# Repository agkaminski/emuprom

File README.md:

# emuprom
DIY ATmega8 based 27C256 EPROM emulator. Human accessible UART interface
(19200N1, CH340 on USB C).

Revision D has been verified and it is working as intended (working both with
TL866 EPROM programer and FellaPC computer).

# Target connection
Via ribbon cable with DIP-28 adapter. Uses 40 pin IDC connector, but only 28
pins are used. Target power state detection is supported (external bus is
resistant to the target high-z bus state).

Crude cable schematic, top view (should be enough to be able to make this cable):

Sanity check - EPROM GND (pin \#14) should be on the one before last wire (bottom of the picture).

# UART interface
Available via USB C UART port, 19200 baud, no parity, 1 stop bit. Interface is
human friendly, but also easy to script. Available commands:

- ? - help
- ! - claim bus, memory edit, assert /RST
- . - release bus, deassert /RST
- @ - set address mode
- \# - set data mode
- = - dump 256 bytes @addres
- t - memory test
- \+ - echo on
- \- echo off
- m - calculate md5 sum
- s - clear memory (all 0xff)
- r - reset target (pulse /RST)

Example sequence with comments:
- \- echo disable,
- ! - claims the bus,
- @0000 - sets address to zero,
- \# - selects data mode,
- 0102030405060708 - 8 bytes are written at address 0,
- . - release the bus and start the target,
- \+ - enable echo.

Or all at once: -!@0000#0102030405060708.+

# Uploading FW
avr-gcc, avr-libc and avrdude are needed.

- make (build FW),
- make fuse (set fuses to set internal RC @8MHz),
- make install (upload FW).

# Pictures
This is a picture of revision D. Note the recommended heat shrink sleeve, to
prevent accidental short circuits.

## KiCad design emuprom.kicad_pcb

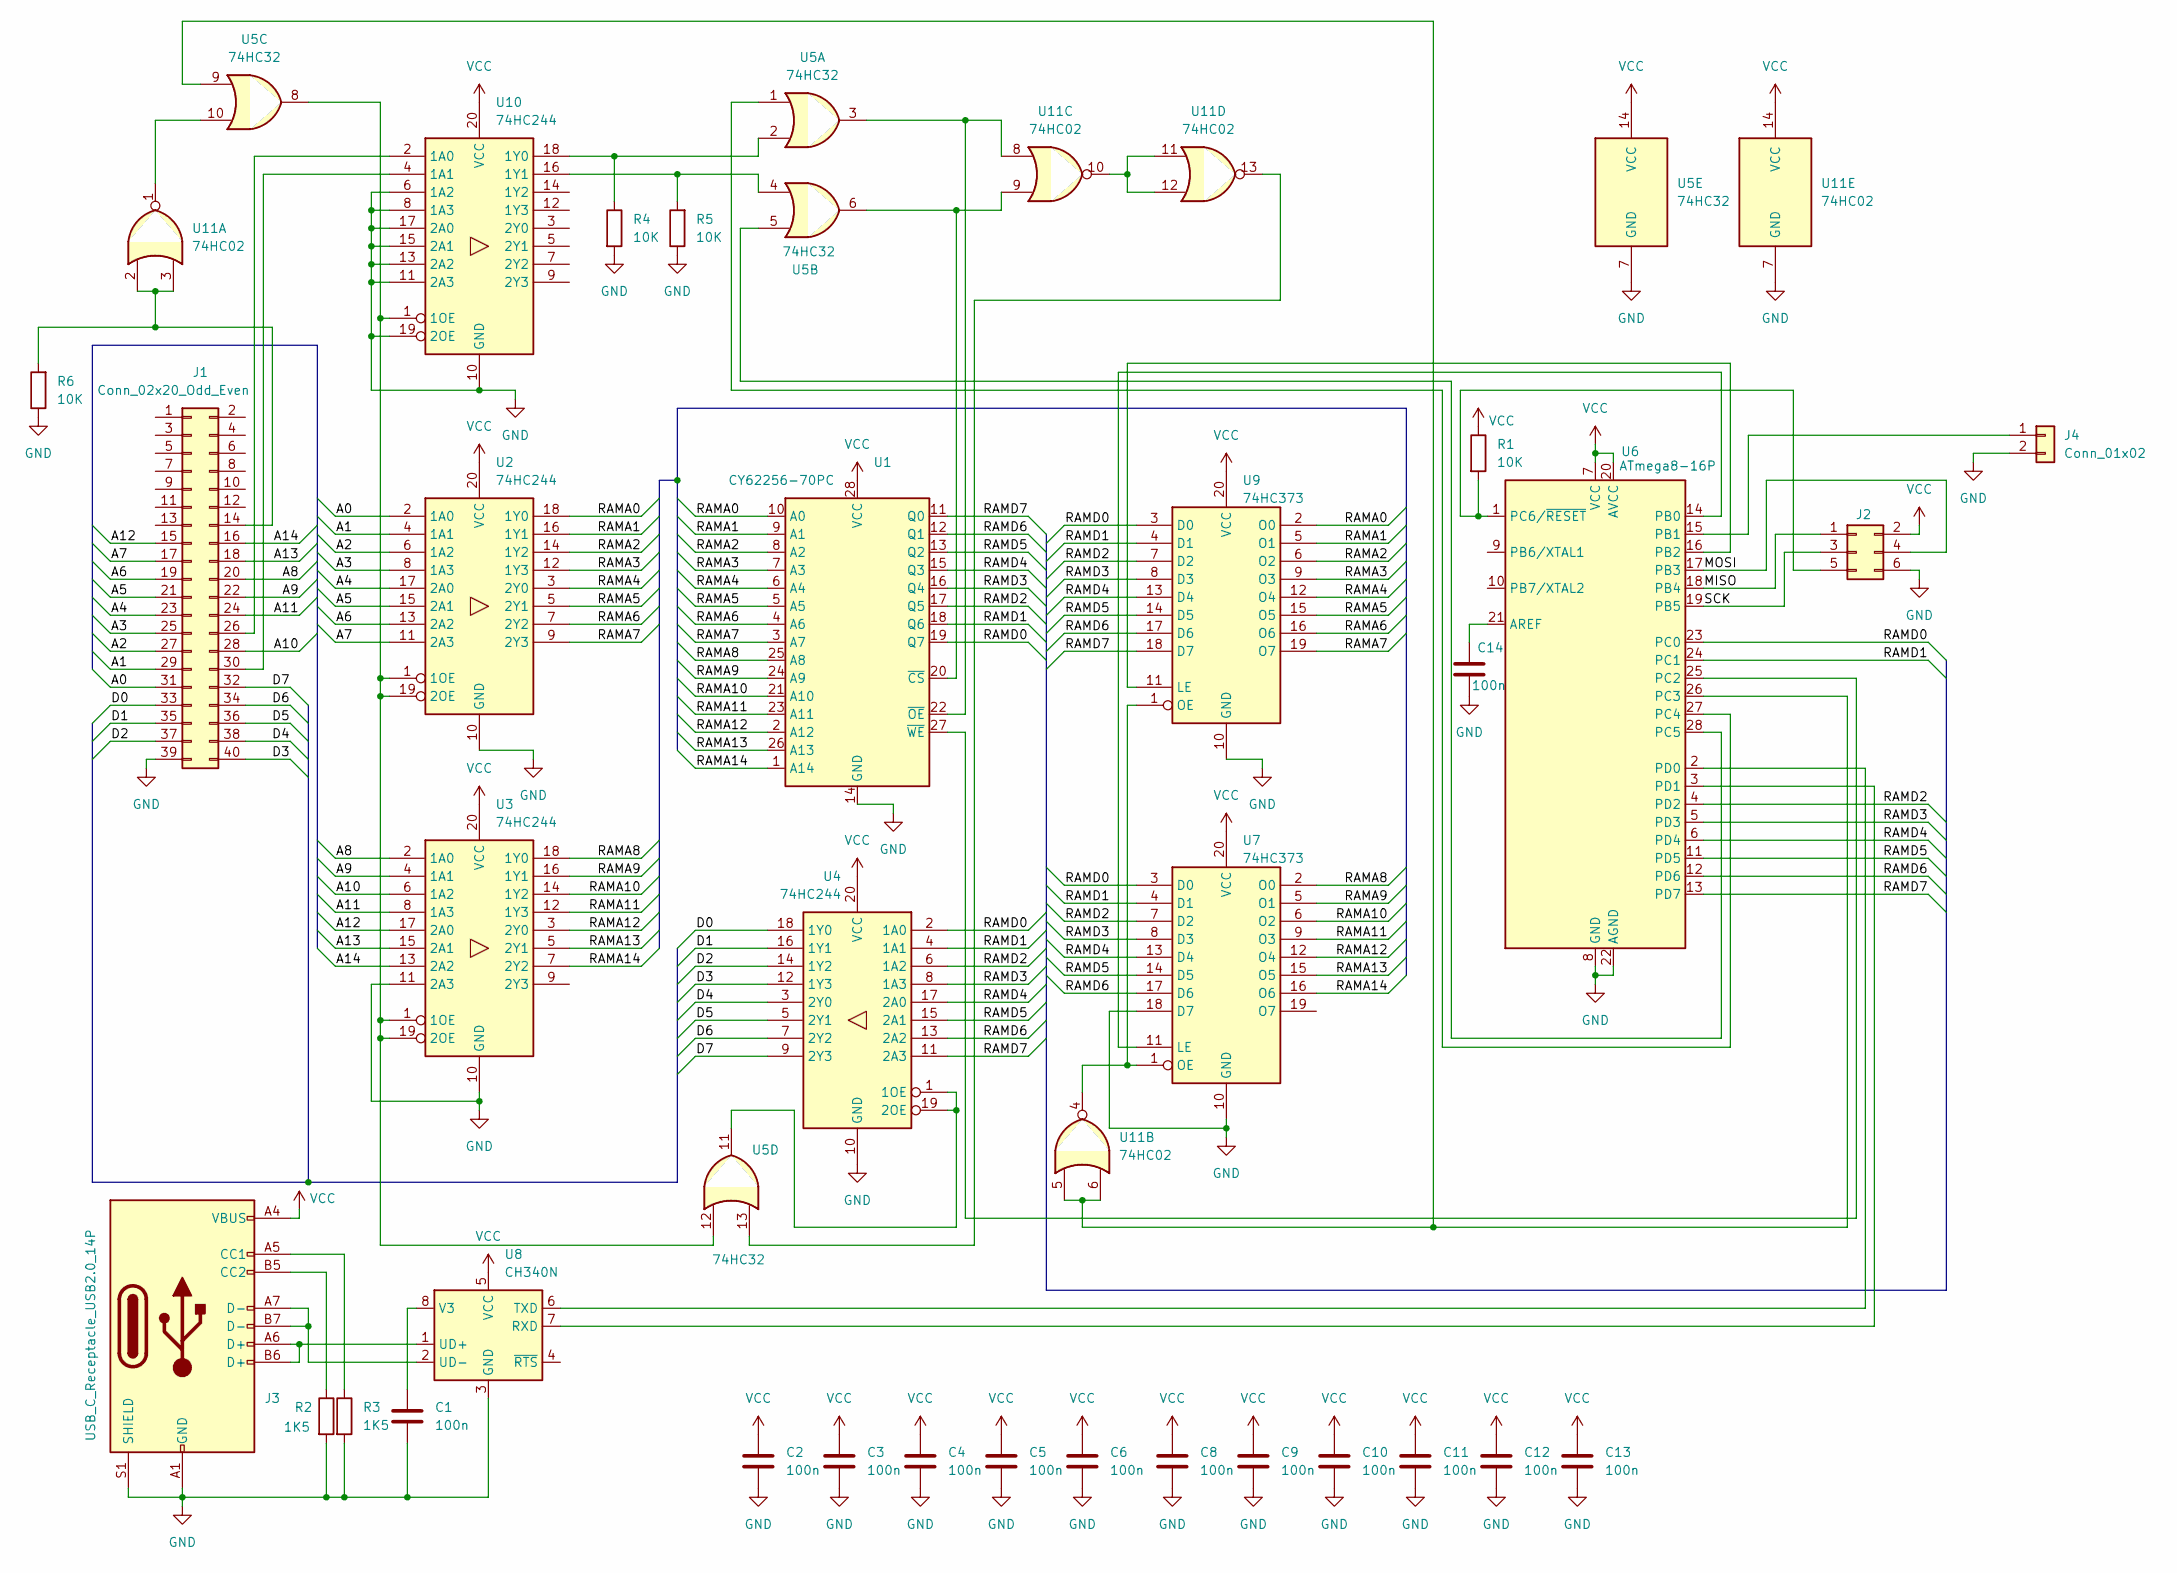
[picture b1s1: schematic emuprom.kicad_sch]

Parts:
C1, C2, C3, C4, C5, C6, C8, C9, C10, C11, C12, C13, C14: 100n; C_Disc_D3.0mm_W1.6mm_P2.50mm
J1: Conn_02x20_Odd_Even; IDC-Header_2x20_P2.54mm_Horizontal
J2: Conn_02x03_Odd_Even; IDC-Header_2x03_P2.54mm_Vertical
J3: USB_C_Receptacle_USB2.0_14P; USB_C_Receptacle_GCT_USB4105-xx-A_16P_TopMnt_Horizontal
J4: Conn_01x02; PinHeader_1x02_P2.54mm_Horizontal
R1, R4, R5, R6: 10K; R_Axial_DIN0207_L6.3mm_D2.5mm_P7.62mm_Horizontal
R2, R3: 1K5; R_Axial_DIN0207_L6.3mm_D2.5mm_P7.62mm_Horizontal
U1: CY62256-70PC; DIP-28_W15.24mm
U2, U3, U4, U10: 74HC244; DIP-20_W7.62mm
U5: 74HC32; DIP-14_W7.62mm
U6: ATmega8-16P; DIP-28_W7.62mm
U7, U9: 74HC373; DIP-20_W7.62mm
U8: CH340N; SOP-8_3.9x4.9mm_P1.27mm
U11: 74HC02; DIP-14_W7.62mm

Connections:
/A0: J1.31, U2.2 (1A0)
/A1: J1.29, U2.4 (1A1)
/A2: J1.27, U2.6 (1A2)
/A3: J1.25, U2.8 (1A3)
/A4: J1.23, U2.17 (2A0)
/A5: J1.21, U2.15 (2A1)
/A6: J1.19, U2.13 (2A2)
/A7: J1.17, U2.11 (2A3)
/A8: J1.20, U3.2 (1A0)
/A9: J1.22, U3.4 (1A1)
/A10: J1.28, U3.6 (1A2)
/A11: J1.24, U3.8 (1A3)
/A12: J1.15, U3.17 (2A0)
/A13: J1.18, U3.15 (2A1)
/A14: J1.16, U3.13 (2A2)
/D0: J1.33, U4.18 (1Y0)
/D1: J1.35, U4.16 (1Y1)
/D2: J1.37, U4.14 (1Y2)
/D3: J1.40, U4.12 (1Y3)
/D4: J1.38, U4.3 (2Y0)
/D5: J1.36, U4.5 (2Y1)
/D6: J1.34, U4.7 (2Y2)
/D7: J1.32, U4.9 (2Y3)
/MISO: J2.1, U6.18 (PB4)
/MOSI: J2.4, U6.17 (PB3)
/RAMA0: U1.10 (A0), U2.18 (1Y0), U9.2 (O0)
/RAMA1: U1.9 (A1), U2.16 (1Y1), U9.5 (O1)
/RAMA2: U1.8 (A2), U2.14 (1Y2), U9.6 (O2)
/RAMA3: U1.7 (A3), U2.12 (1Y3), U9.9 (O3)
/RAMA4: U1.6 (A4), U2.3 (2Y0), U9.12 (O4)
/RAMA5: U1.5 (A5), U2.5 (2Y1), U9.15 (O5)
/RAMA6: U1.4 (A6), U2.7 (2Y2), U9.16 (O6)
/RAMA7: U1.3 (A7), U2.9 (2Y3), U9.19 (O7)
/RAMA8: U1.25 (A8), U3.18 (1Y0), U7.2 (O0)
/RAMA9: U1.24 (A9), U3.16 (1Y1), U7.5 (O1)
/RAMA10: U1.21 (A10), U3.14 (1Y2), U7.6 (O2)
/RAMA11: U1.23 (A11), U3.12 (1Y3), U7.9 (O3)
/RAMA12: U1.2 (A12), U3.3 (2Y0), U7.12 (O4)
/RAMA13: U1.26 (A13), U3.5 (2Y1), U7.15 (O5)
/RAMA14: U1.1 (A14), U3.7 (2Y2), U7.16 (O6)
/RAMD0: U1.19 (Q7), U4.2 (1A0), U6.23 (PC0), U7.3 (D0), U9.3 (D0)
/RAMD1: U1.18 (Q6), U4.4 (1A1), U6.24 (PC1), U7.4 (D1), U9.4 (D1)
/RAMD2: U1.17 (Q5), U4.6 (1A2), U6.4 (PD2), U7.7 (D2), U9.7 (D2)
/RAMD3: U1.16 (Q4), U4.8 (1A3), U6.5 (PD3), U7.8 (D3), U9.8 (D3)
/RAMD4: U1.15 (Q3), U4.17 (2A0), U6.6 (PD4), U7.13 (D4), U9.13 (D4)
/RAMD5: U1.13 (Q2), U4.15 (2A1), U6.11 (PD5), U7.14 (D5), U9.14 (D5)
/RAMD6: U1.12 (Q1), U4.13 (2A2), U6.12 (PD6), U7.17 (D6), U9.17 (D6)
/RAMD7: U1.11 (Q0), U4.11 (2A3), U6.13 (PD7), U9.18 (D7)
/SCK: J2.3, U6.19 (PB5)
GND: C1.2, C2.2, C3.2, C4.2, C5.2, C6.2, C8.2, C9.2, C10.2, C11.2, C12.2, C13.2, C14.2, J1.39, J2.6, J3.A1 (GND), J3.A12 (GND), J3.B1 (GND), J3.B12 (GND), J3.S1 (SHIELD), J4.2, R2.2, R3.2, R4.2, R5.1, R6.1, U1.14 (GND), U2.10 (GND), U3.10 (GND), U3.11 (2A3), U4.10 (GND), U5.7 (GND), U6.8 (GND), U6.22 (AGND), U7.10 (GND), U7.18 (D7), U8.3 (GND), U9.10 (GND), U10.6 (1A2), U10.8 (1A3), U10.10 (GND), U10.11 (2A3), U10.13 (2A2), U10.15 (2A1), U10.17 (2A0), U10.19 (2OE), U11.7 (GND)
unnamed: J1.14, R6.2, U11.2, U11.3
unnamed: J1.26, U10.2 (1A0)
unnamed: J1.30, U10.4 (1A1)
unnamed: J2.5, R1.2, U6.1 (PC6/~RESET)
unnamed: J3.A5 (CC1), R3.1
unnamed: J3.B5 (CC2), R2.1
unnamed: J4.1, U6.15 (PB1)
unnamed: U1.20 (~CS), U5.6, U11.9
unnamed: U1.22 (~OE), U5.3, U11.8
unnamed: U1.27 (~WE), U6.25 (PC2)
unnamed: U4.1 (1OE), U4.19 (2OE), U5.11
unnamed: C14.1, U6.21 (AREF)
unnamed: U6.14 (PB0), U7.11 (LE)
unnamed: U6.16 (PB2), U9.11 (LE)
unnamed: U5.9, U6.26 (PC3), U11.5, U11.6
unnamed: U5.1, U6.27 (PC4)
unnamed: U5.5, U6.28 (PC5)
unnamed: U6.2 (PD0), U8.6 (TXD)
unnamed: U6.3 (PD1), U8.7 (RXD)
unnamed: U7.1 (OE), U9.1 (OE), U11.4
unnamed: J3.A6 (D+), J3.B6 (D+), U8.1 (UD+)
unnamed: J3.A7 (D-), J3.B7 (D-), U8.2 (UD-)
unnamed: C1.1, U8.8 (V3)
unnamed: U2.1 (1OE), U2.19 (2OE), U3.1 (1OE), U3.19 (2OE), U5.8, U5.12, U10.1 (1OE)
unnamed: R4.1, U5.2, U10.18 (1Y0)
unnamed: R5.2, U5.4, U10.16 (1Y1)
unnamed: U5.10, U11.1
unnamed: U11.10, U11.11, U11.12
unnamed: U5.13, U11.13
VCC: C2.1, C3.1, C4.1, C5.1, C6.1, C8.1, C9.1, C10.1, C11.1, C12.1, C13.1, J2.2, J3.A4 (VBUS), J3.A9 (VBUS), J3.B4 (VBUS), J3.B9 (VBUS), R1.1, U1.28 (VCC), U2.20 (VCC), U3.20 (VCC), U4.20 (VCC), U5.14 (VCC), U6.7 (VCC), U6.20 (AVCC), U7.20 (VCC), U8.5 (VCC), U9.20 (VCC), U10.20 (VCC), U11.14 (VCC)

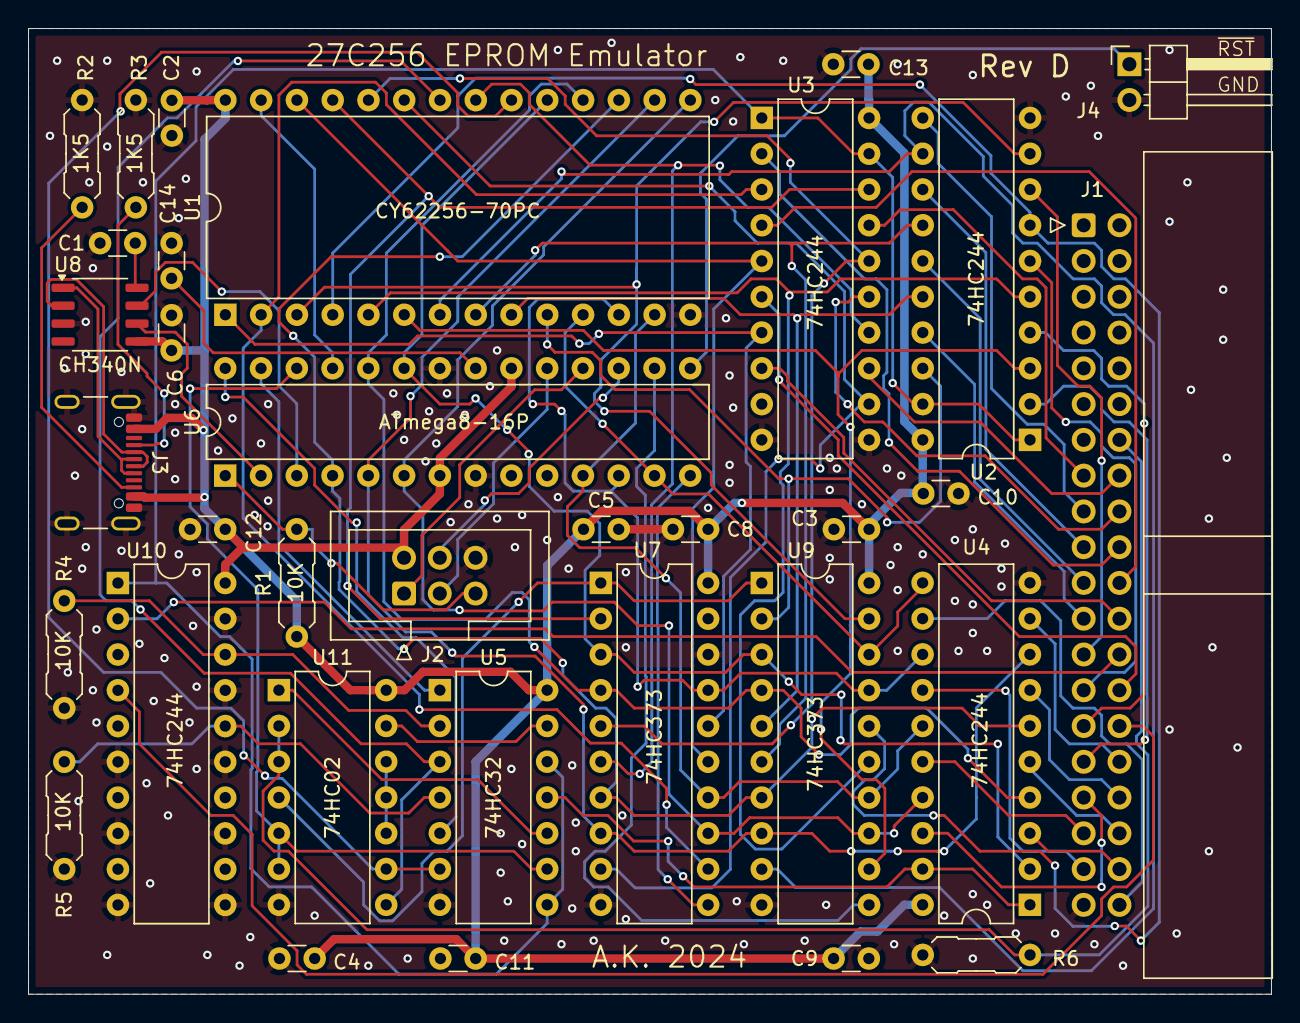
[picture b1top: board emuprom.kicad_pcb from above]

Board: 2 copper layers, 88.3 x 68.6 mm, 34 parts (0 on the bottom side), 80 nets.

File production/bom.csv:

Designator,Footprint,Quantity,Value,LCSC Part #
"C1, C10, C11, C12, C13, C14, C2, C3, C4, C5, C6, C8, C9",C_Disc_D3.0mm_W1.6mm_P2.50mm,13,100n,
J1,IDC-Header_2x20_P2.54mm_Horizontal,1,Conn_02x20_Odd_Even,
J2,IDC-Header_2x03_P2.54mm_Vertical,1,Conn_02x03_Odd_Even,
J3,USB_C_Receptacle_GCT_USB4105-xx-A_16P_TopMnt_Horizontal,1,USB_C_Receptacle_USB2.0_14P,
J4,PinHeader_1x02_P2.54mm_Horizontal,1,Conn_01x02,
"R1, R4, R5, R6",R_Axial_DIN0207_L6.3mm_D2.5mm_P7.62mm_Horizontal,4,10K,
"R2, R3",R_Axial_DIN0207_L6.3mm_D2.5mm_P7.62mm_Horizontal,2,1K5,
U1,DIP-28_W15.24mm,1,CY62256-70PC,
"U10, U2, U3, U4",DIP-20_W7.62mm,4,74HC244,
U11,DIP-14_W7.62mm,1,74HC02,
U5,DIP-14_W7.62mm,1,74HC32,
U6,DIP-28_W7.62mm,1,ATmega8-16P,
"U7, U9",DIP-20_W7.62mm,2,74HC373,
U8,SOP-8_3.9x4.9mm_P1.27mm,1,CH340N,

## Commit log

2024-03-30 Initial import
2024-03-30 Readme fixes
2024-03-30 Remove not needed files
2024-04-03 Fix HW bug
    U4 direction pin was tied to the wrong signal -
    should be /RD instead of /WR. Tied it to the ground
    instead. Now U4 74HC245 should be replaced with
    74HC244, but it would require big layout change, so
    I'm leaving it as is.
2024-04-03 Add caution about rev A
2024-04-03 FW: Add MD5 sum feature
2024-04-03 Add adapter cable info and update readme
2024-04-03 Add AVR FW hex blob
2024-04-03 Fix readme typo
2024-04-04 Revision C: redesign to fix U4 problem
    Reduced PCB footprint slightly, change U11 74HC04 -> 74HC02
2024-04-17 rev D: Fix U4 output being swapped with input
2024-04-27 Update readme and image about revision D
